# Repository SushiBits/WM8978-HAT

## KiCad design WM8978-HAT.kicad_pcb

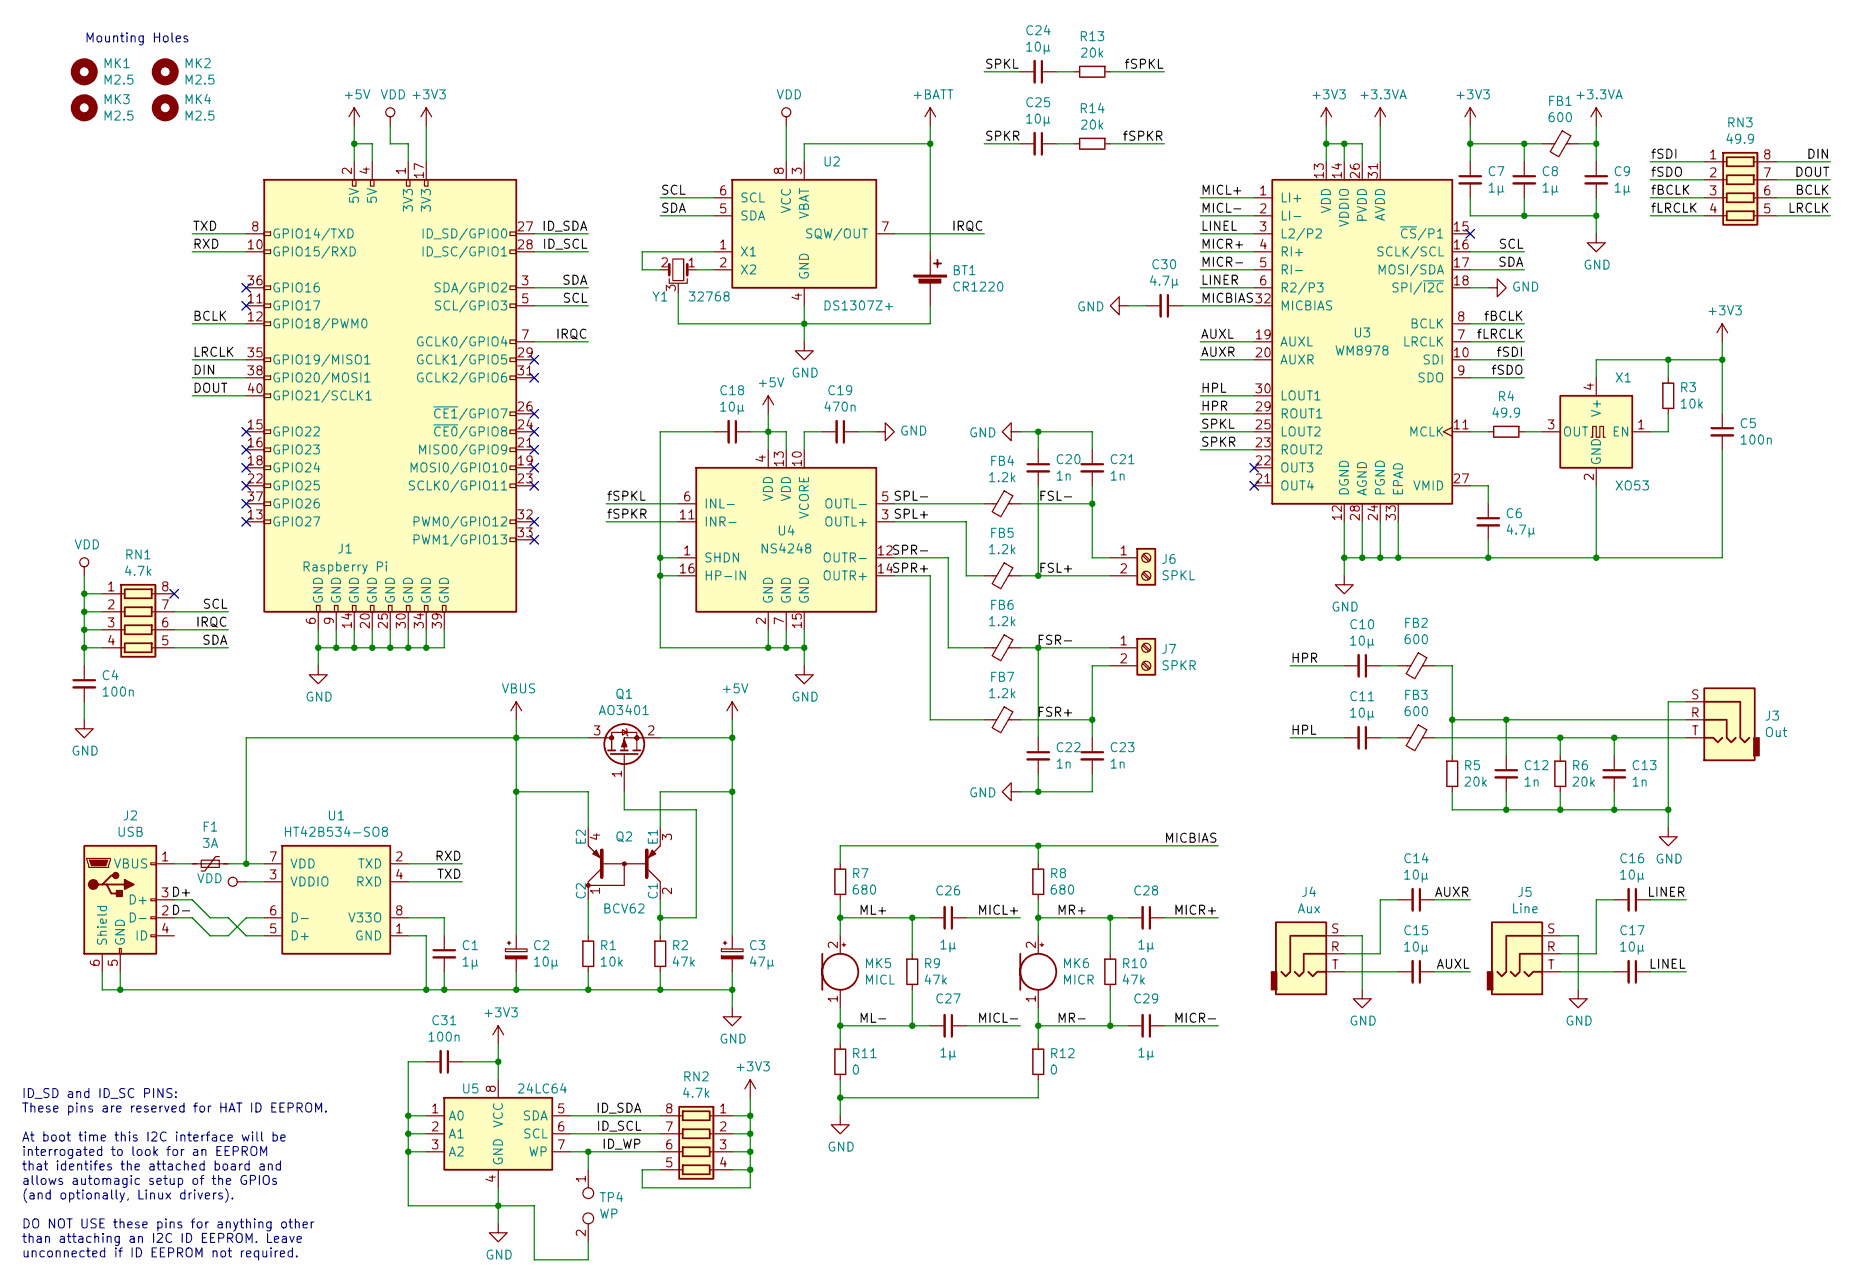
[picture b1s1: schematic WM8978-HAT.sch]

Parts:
BT1: CR1220; BatteryHolder_QJ1220_1x1220
C1, C7, C8, C9, C26, C27, C28, C29: 1µ; C_0603_1608Metric_Pad1.05x0.95mm_HandSolder
C2: 10µ; CP_EIA-3528-21_Kemet-B
C3: 47µ; CP_EIA-3528-21_Kemet-B
C4, C5, C31: 100n; C_0603_1608Metric_Pad1.05x0.95mm_HandSolder
C6, C30: 4.7µ; C_0603_1608Metric_Pad1.05x0.95mm_HandSolder
C10, C11, C14, C15, C16, C17, C18, C24, C25: 10µ; C_0603_1608Metric_Pad1.05x0.95mm_HandSolder
C12, C13, C20, C21, C22, C23: 1n; C_0603_1608Metric_Pad1.05x0.95mm_HandSolder
C19: 470n; C_0603_1608Metric_Pad1.05x0.95mm_HandSolder
F1: 3A; Fuse_1812_4532Metric_Pad1.30x3.40mm_HandSolder
FB1, FB2, FB3: 600; L_0603_1608Metric_Pad1.05x0.95mm_HandSolder
FB4, FB5, FB6, FB7: 1.2k; L_0603_1608Metric_Pad1.05x0.95mm_HandSolder
J1: Raspberry Pi; PinSocket_2x20_P2.54mm_Vertical
J2: USB; USB_Micro-B_Molex-105017-0001
J3: Out; PJ3130
J4: Aux; PJ3130
J5: Line; PJ3130
J6: SPKL; TerminalBlock_Phoenix_MKDS-1,5-2-5.08_1x02_P5.08mm_Horizont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
J7: SPKR; TerminalBlock_Phoenix_MKDS-1,5-2-5.08_1x02_P5.08mm_Horizont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
MK1, MK2, MK3, MK4: M2.5; MountingHole_2.7mm_M2.5
MK5: MICL; GMI6027P
MK6: MICR; GMI6027P
Q1: AO3401; SOT-23W
Q2: BCV62; SOT-143
R1, R3: 10k; R_0603_1608Metric_Pad1.05x0.95mm_HandSolder
R2, R9, R10: 47k; R_0603_1608Metric_Pad1.05x0.95mm_HandSolder
R4: 49.9; R_0603_1608Metric_Pad1.05x0.95mm_HandSolder
R5, R6, R13, R14: 20k; R_0603_1608Metric_Pad1.05x0.95mm_HandSolder
R7, R8: 680; R_0603_1608Metric_Pad1.05x0.95mm_HandSolder
R11, R12: 0; R_0603_1608Metric_Pad1.05x0.95mm_HandSolder
RN1, RN2: 4.7k; R_Array_Convex_4x0603
RN3: 49.9; R_Array_Convex_4x0603
TP4: WP; PinHeader_1x02_P2.54mm_Vertical
U1: HT42B534-SO8; SOIC-8_3.9x4.9mm_P1.27mm
U2: DS1307Z+; SOIC-8_3.9x4.9mm_P1.27mm
U3: WM8978; QFN-32-1EP_5x5mm_P0.5mm_EP3.45x3.45mm
U4: NS4248; SOIC-16_3.9x9.9mm_P1.27mm
U5: 24LC64; SOIC-8_3.9x4.9mm_P1.27mm
X1: XO53; Oscillator_SMD_EuroQuartz_XO53-4Pin_5.0x3.2mm_HandSoldering
Y1: 32768; Crystal_C26-LF_D2.1mm_L6.5mm_Horizontal_1EP_style1

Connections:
+3.3VA: C9.1, FB1.1, U3.31 (AVDD)
+3V3: C5.1, C7.1, C8.1, C31.1, FB1.2, J1.17 (3V3), R3.1, RN2.1 (R1.1), RN2.2 (R2.1), RN2.3 (R3.1), RN2.4 (R4.1), RN2.5 (R4.2), U3.13 (VDD), U3.14 (VDDIO), U3.26 (PVDD), U5.8 (VCC), X1.4 (V+)
+5V: C3.1, C18.1, J1.2 (5V), J1.4 (5V), Q1.2 (S), Q2.3 (E1), U4.4 (VDD), U4.13 (VDD)
+BATT: BT1.1 (+), U2.3 (VBAT)
/AUXL: C15.1, U3.19 (AUXL)
/AUXR: C14.1, U3.20 (AUXR)
/BCLK: J1.12 (GPIO18/PWM0), RN3.6 (R3.2)
/D+: J2.3 (D+), U1.5 (D+)
/D-: J2.2 (D-), U1.6 (D-)
/DIN: J1.38 (GPIO20/MOSI1), RN3.8 (R1.2)
/DOUT: J1.40 (GPIO21/SCLK1), RN3.7 (R2.2)
/FSL+: C20.2, FB5.1, J6.2
/FSL-: C21.2, FB4.1, J6.1
/FSR+: C23.1, FB7.1, J7.2
/FSR-: C22.1, FB6.1, J7.1
/HPL: C11.2, U3.30 (LOUT1)
/HPR: C10.2, U3.29 (ROUT1)
/ID_SCL: J1.28 (ID_SC/GPIO1), RN2.7 (R2.2), U5.6 (SCL)
/ID_SDA: J1.27 (ID_SD/GPIO0), RN2.8 (R1.2), U5.5 (SDA)
/ID_WP: RN2.6 (R3.2), TP4.1, U5.7 (WP)
/IRQC: J1.7 (GCLK0/GPIO4), RN1.6 (R3.2), U2.7 (SQW/OUT)
/LINEL: C17.1, U3.3 (L2/P2)
/LINER: C16.1, U3.6 (R2/P3)
/LRCLK: J1.35 (GPIO19/MISO1), RN3.5 (R4.2)
/MICBIAS: C30.1, R7.1, R8.1, U3.32 (MICBIAS)
/MICL+: C26.1, U3.1 (LI+)
/MICL-: C27.1, U3.2 (LI-)
/MICR+: C28.1, U3.4 (RI+)
/MICR-: C29.1, U3.5 (RI-)
/ML+: C26.2, MK5.2 (+), R7.2, R9.1
/ML-: C27.2, MK5.1 (-), R9.2, R11.1
/MR+: C28.2, MK6.2 (+), R8.2, R10.1
/MR-: C29.2, MK6.1 (-), R10.2, R12.1
/RXD: J1.10 (GPIO15/RXD), U1.2 (TXD)
/SCL: J1.5 (SCL/GPIO3), RN1.7 (R2.2), U2.6 (SCL), U3.16 (SCLK/SCL)
/SDA: J1.3 (SDA/GPIO2), RN1.5 (R4.2), U2.5 (SDA), U3.17 (MOSI/SDA)
/SPKL: C24.2, U3.25 (LOUT2)
/SPKR: C25.2, U3.23 (ROUT2)
/SPL+: FB5.2, U4.3 (OUTL+)
/SPL-: FB4.2, U4.5 (OUTL-)
/SPR+: FB7.2, U4.14 (OUTR+)
/SPR-: FB6.2, U4.12 (OUTR-)
/TXD: J1.8 (GPIO14/TXD), U1.4 (RXD)
/fBCLK: RN3.3 (R3.1), U3.8 (BCLK)
/fLRCLK: RN3.4 (R4.1), U3.7 (LRCLK)
/fSDI: RN3.1 (R1.1), U3.10 (SDI)
/fSDO: RN3.2 (R2.1), U3.9 (SDO)
/fSPKL: R13.1, U4.6 (INL-)
/fSPKR: R14.1, U4.11 (INR-)
GND: BT1.2 (-), C1.2, C2.2, C3.2, C4.2, C5.2, C6.2, C7.2, C8.2, C9.2, C12.2, C13.2, C18.2, C19.1, C20.1, C21.1, C22.2, C23.2, C30.2, C31.2, J1.6 (GND), J1.9 (GND), J1.14 (GND), J1.20 (GND), J1.25 (GND), J1.30 (GND), J1.34 (GND), J1.39 (GND), J2.5 (GND), J2.6 (Shield), J3.S, J4.S, J5.S, R1.2, R2.2, R5.2, R6.2, R11.2, R12.2, TP4.2, U1.1 (GND), U2.4 (GND), U3.12 (DGND), U3.18 (SPI/~I2C), U3.24 (PGND), U3.28 (AGND), U3.33 (EPAD), U4.1 (SHDN), U4.2 (GND), U4.7 (GND), U4.15 (GND), U4.16 (HP-IN), U5.1 (A0), U5.2 (A1), U5.3 (A2), U5.4 (GND), X1.2 (GND), Y1.3
unnamed: C1.1, U1.8 (V33O)
unnamed: C6.1, U3.27 (VMID)
unnamed: C10.1, FB2.2
unnamed: C11.1, FB3.2
unnamed: C12.1, FB2.1, J3.R, R5.1
unnamed: C13.1, FB3.1, J3.T, R6.1
unnamed: C14.2, J4.R
unnamed: C15.2, J4.T
unnamed: C16.2, J5.R
unnamed: C17.2, J5.T
unnamed: C19.2, U4.10 (VCORE)
unnamed: C24.1, R13.2
unnamed: C25.1, R14.2
unnamed: F1.2, J2.1 (VBUS)
unnamed: Q1.1 (G), Q2.2 (C1), R2.1
unnamed: Q2.1 (C2), R1.1
unnamed: R3.2, X1.1 (EN)
unnamed: R4.1, X1.3 (OUT)
unnamed: R4.2, U3.11 (MCLK)
unnamed: U2.1 (X1), Y1.2
unnamed: U2.2 (X2), Y1.1
VBUS: C2.1, F1.1, Q1.3 (D), Q2.4 (E2), U1.7 (VDD)
VDD: C4.1, J1.1 (3V3), RN1.1 (R1.1), RN1.2 (R2.1), RN1.3 (R3.1), RN1.4 (R4.1), U1.3 (VDDIO), U2.8 (VCC)

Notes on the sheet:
ID_SD and ID_SC PINS: These pins are reserved for HAT ID EEPROM. At boot time this I2C interface will be interrogated to look for an EEPROM that identifes the attached board and allows automagic setup of the GPIOs (and optionally, Linux drivers). DO NOT USE these pins for anything other than attach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
Mounting Holes

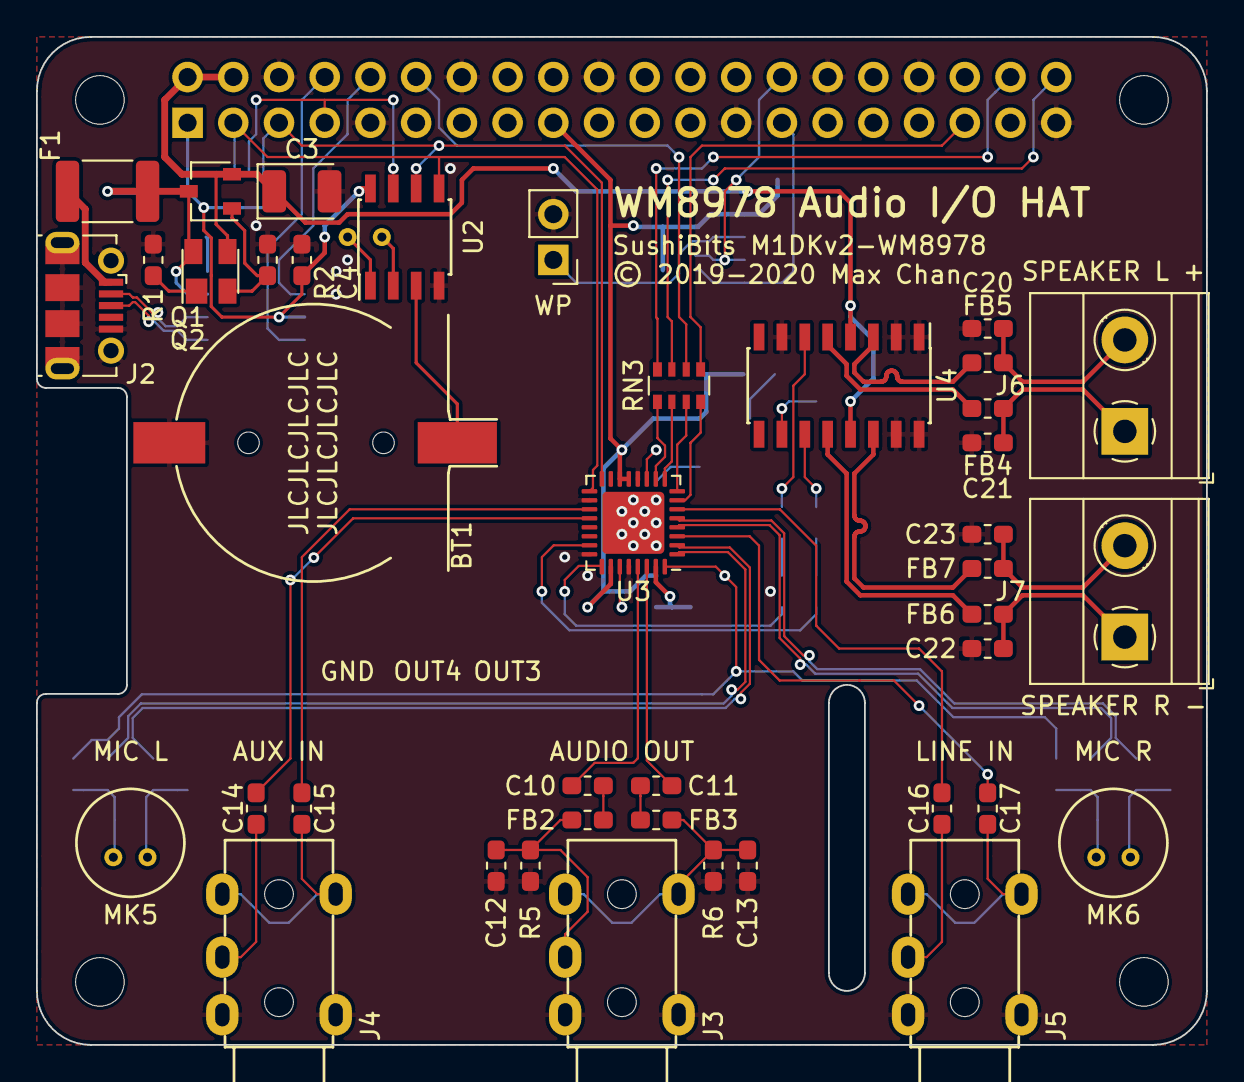
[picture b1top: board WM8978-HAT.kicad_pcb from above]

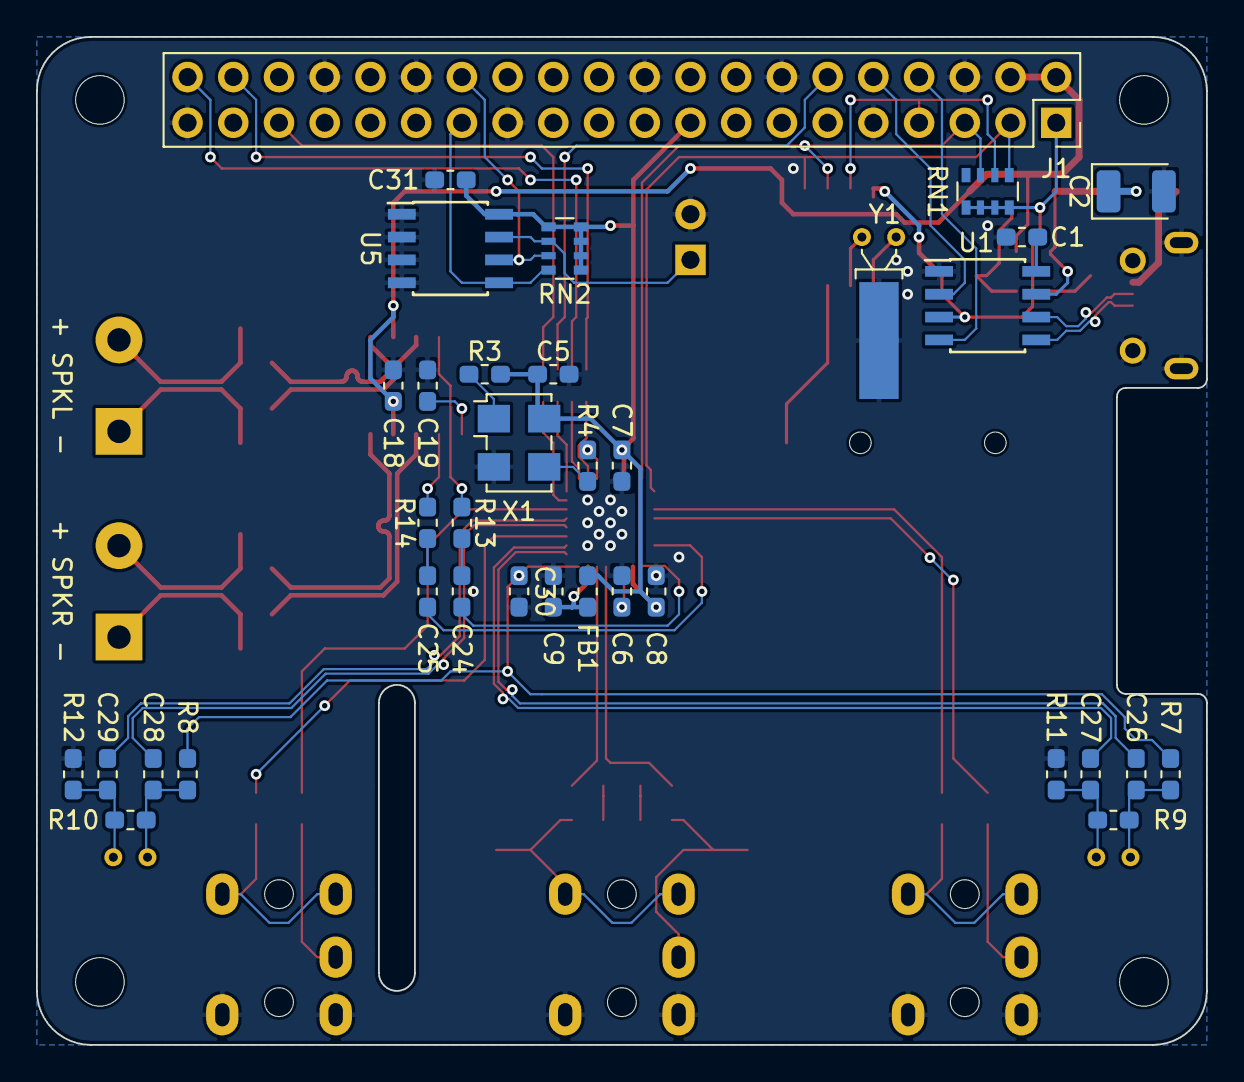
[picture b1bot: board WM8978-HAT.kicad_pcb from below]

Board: 2 copper layers, 65.0 x 56.0 mm, 80 parts (35 on the bottom side), 73 nets.

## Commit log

2020-06-06 Code drop: WM8978 HAT Design
2020-06-06 HAT Makefile
2020-06-06 Makefile for dtbo and eeprom files

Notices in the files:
WM8978-HAT.kicad_pcb:
© 2019-2020 Max Chan
